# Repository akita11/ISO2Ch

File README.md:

# ISO2ch

Chipanalog社のデジタルアイソレータ[CA-IS3642HW](https://www.lcsc.com/product-detail/Digital-Isolators-with-power_Chipanalog-CA-IS3642HW_C2890053.html)を使った2チャンネルのデジタルアイソレータです。電源と2本のデジタル信号線を電気的に絶縁（分離）することができます。使用しているCA-1364の仕様上、直流から150MHzまでのデジタル信号を伝送できます。

入出力はGroveコネクタで、出力側の電源電圧は5Vと3.3Vから選択でき、また2本のデジタル信号の向きを変更することができます。

## 基本的な使い方

裏面で、2つのGroveコネクタの種別を確認します。一方が電源の給電側、もう1方が電源の受電側です。
給電側のGroveコネクタに、電源を供給する側の機器（M5Stack等）を接続します。
受電側のGroveコネクタに、電源を受ける側の機器（センサ等）を接続します。受電側には5Vの電源（または3.3Vにも設定可能）が供給されます。

Groveコネクタの2本の信号線の信号（デジタル信号）の向きは、初期状態では2本とも「給電側＝入力／受電側＝出力」となっています。なお入力信号が未接続のときは出力側は"H"となります。（信号の向き後述のように半田ジャンパで変更できます）※仕様上、I2Cのように双方向の通信が必要な場合には使用できません

給電側・受電側のGroveコネクタのピン配置は以下のとおりです。

- 1: B (デジタル信号線1)
- 2: A (デジタル信号線2)
- 3: VDD
- 4: GND

## 設定変更の方法

### 受電側の電源電圧

表面のJP5で、受電側の電源電圧を設定できます。

- 中央-△マークのある側をショート（初期状態）: 5V
- 中央-△マークのない側をショート: 3.3V （※中央-△マークのある側の基板パターンをカットしてください）

### デジタル信号の方向

裏面のJP1/2/3/4で、2本のデジタル信号線の信号の向きを設定できます。

- B（デジタル信号線1）
 - JP1とJP4の中央-△マークのある側をショート（初期状態）：給電側＝入力、受電側＝出力
 - JP1とJP4の中央-△マークのない側をショート：給電側＝出力、受電側＝入力（※中央-△マークのある側の基板パターンをカットしてください）

- A（デジタル信号線2）
 - JP2とJP3の中央-△マークのある側をショート（初期状態）：給電側＝入力、受電側＝出力
 - JP2とJP3の中央-△マークのない側をショート：給電側＝出力、受電側＝入力（※中央-△マークのある側の基板パターンをカットしてください）

## Author

Junichi Akita (@akita11, akita@ifdl.jp)

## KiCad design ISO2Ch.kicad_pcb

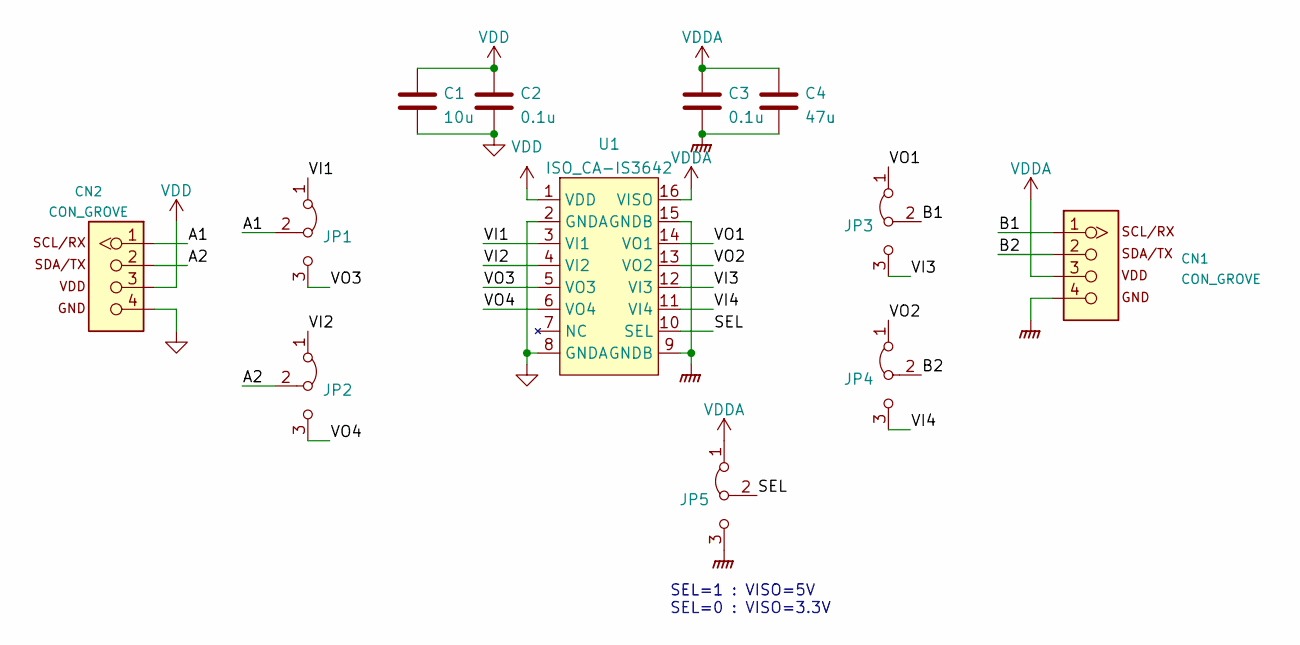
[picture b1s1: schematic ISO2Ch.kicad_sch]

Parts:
C1: 10u; C_0603_1608Metric; LCSC C109454
C2, C3: 0.1u; C_0603_1608Metric; LCSC C14663
C4: 47u; C_0805_2012Metric; LCSC C19103846
CN1, CN2: CON_GROVE; CON_GROVE_H
JP1, JP2, JP3, JP4, JP5: Jumper_3_Bridged12; SolderJumper-3_P1.3mm_Bridged12_RoundedPad1.0x1.5mm
U1: ISO_CA-IS3642; SOIC-16W_7.5x10.3mm_P1.27mm; LCSC C2890053

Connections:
/A1: CN2.1, JP1.2 (C)
/A2: CN2.2, JP2.2 (C)
/B1: CN1.1, JP3.2 (C)
/B2: CN1.2, JP4.2 (C)
/SEL: JP5.2 (C), U1.10 (SEL)
/VI1: JP1.1 (A), U1.3 (VI1)
/VI2: JP2.1 (A), U1.4 (VI2)
/VI3: JP3.3 (B), U1.12 (VI3)
/VI4: JP4.3 (B), U1.11 (VI4)
/VO1: JP3.1 (A), U1.14 (VO1)
/VO2: JP4.1 (A), U1.13 (VO2)
/VO3: JP1.3 (B), U1.5 (VO3)
/VO4: JP2.3 (B), U1.6 (VO4)
GND: C1.2, C2.2, CN2.4, U1.2 (GNDA), U1.8 (GNDA)
GNDPWR: C3.2, C4.2, CN1.4, JP5.3 (B), U1.9 (GNDB), U1.15 (GNDB)
VDD: C1.1, C2.1, CN2.3, U1.1 (VDD)
VDDA: C3.1, C4.1, CN1.3, JP5.1 (A), U1.16 (VISO)

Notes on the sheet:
SEL=1 : VISO=5V SEL=0 : VISO=3.3V

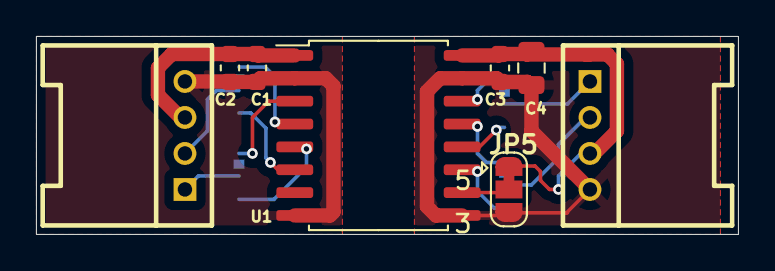
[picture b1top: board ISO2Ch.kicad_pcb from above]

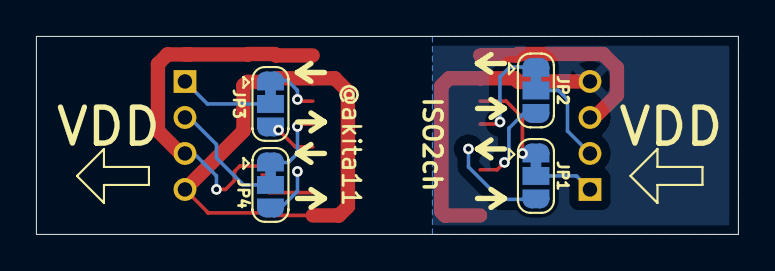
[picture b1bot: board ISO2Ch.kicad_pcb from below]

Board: 2 copper layers, 39.0 x 11.0 mm, 12 parts (4 on the bottom side), 17 nets.

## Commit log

2024-07-03 add photo
